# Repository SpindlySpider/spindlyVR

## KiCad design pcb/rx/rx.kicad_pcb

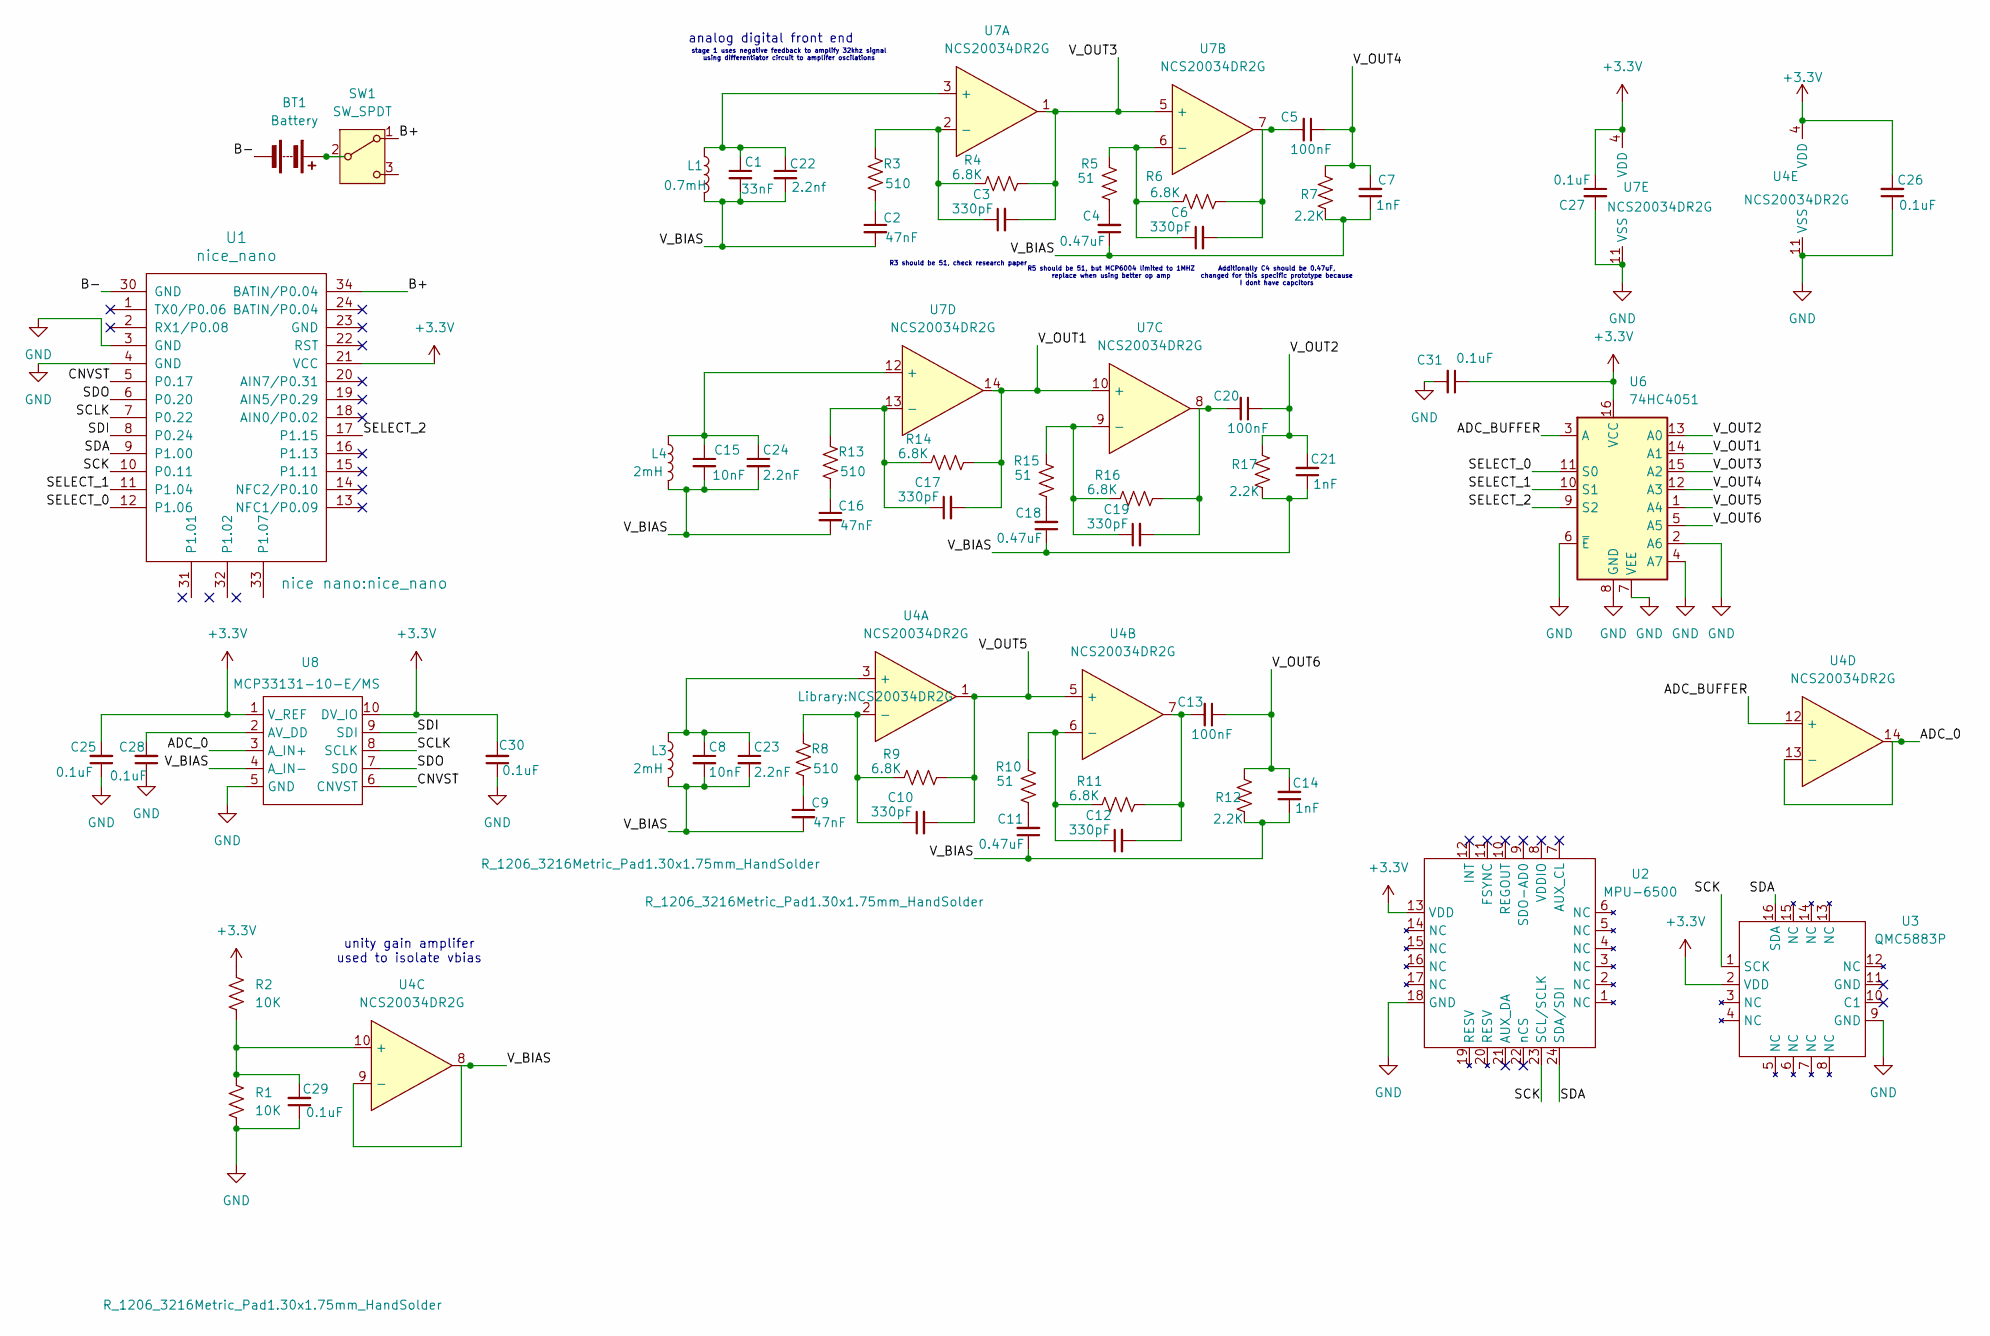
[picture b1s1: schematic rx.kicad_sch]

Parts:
BT1: Battery; JST_PH_B2B-PH-K_1x02_P2.00mm_Vertical
C1: 33nF; C_1206_3216Metric_Pad1.33x1.80mm_HandSolder
C2, C9, C16: 47nF; C_1206_3216Metric_Pad1.33x1.80mm_HandSolder
C3, C6, C10, C12, C17, C19: 330pF; C_1206_3216Metric_Pad1.33x1.80mm_HandSolder
C4, C11, C18: 0.47uF; C_1206_3216Metric_Pad1.33x1.80mm_HandSolder
C5, C13, C20: 100nF; C_1206_3216Metric_Pad1.33x1.80mm_HandSolder
C7, C14, C21: 1nF; C_1206_3216Metric_Pad1.33x1.80mm_HandSolder
C8, C15: 10nF; C_1206_3216Metric_Pad1.33x1.80mm_HandSolder
C22: 2.2nf; C_1206_3216Metric_Pad1.33x1.80mm_HandSolder
C23, C24: 2.2nF; C_1206_3216Metric_Pad1.33x1.80mm_HandSolder
C25, C26, C27, C28, C29, C30, C31: 0.1uF; C_1206_3216Metric_Pad1.33x1.80mm_HandSolder
L1: 0.7mH; R_1206_3216Metric_Pad1.30x1.75mm_HandSolder
L3, L4: 2mH; R_1206_3216Metric_Pad1.30x1.75mm_HandSolder
R1, R2: 10K; R_1206_3216Metric_Pad1.30x1.75mm_HandSolder
R3, R8, R13: 510; R_1206_3216Metric_Pad1.30x1.75mm_HandSolder
R4, R6, R9, R11, R14, R16: 6.8K; R_1206_3216Metric_Pad1.30x1.75mm_HandSolder
R5, R10, R15: 51; R_1206_3216Metric_Pad1.30x1.75mm_HandSolder
R7, R12, R17: 2.2K; R_1206_3216Metric_Pad1.30x1.75mm_HandSolder
SW1: SW_SPDT; EG1218
U1: nice_nano
U2: MPU-6500
U3: QMC5883P
U4, U7: NCS20034DR2G
U6: 74HC4051; 74HC4051-chip
U8: MCP33131-10-E/MS; MCP33131

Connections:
+3.3V: C25.2, C26.2, C27.1, C30.2, C31.1, R2.1, U1.21 (VCC), U2.13 (VDD), U3.2 (VDD), U4.4 (VDD), U6.16 (VCC), U7.4 (VDD), U8.1 (V_REF), U8.10 (DV_IO)
/ADC_0: U4.13 (-), U4.14, U8.3 (A_IN+)
/ADC_BUFFER: U4.12 (+), U6.3 (A)
/B+: SW1.1 (A), U1.34 (BATIN/P0.04)
/B-: BT1.2 (-), U1.30 (GND)
/CNVST: U1.5 (P0.17), U8.6 (CNVST)
/SCK: U1.10 (P0.11), U2.23 (SCL/SCLK), U3.1 (SCK)
/SCLK: U1.7 (P0.22), U8.8 (SCLK)
/SDA: U1.9 (P1.00), U2.24 (SDA/SDI), U3.16 (SDA)
/SDI: U1.8 (P0.24), U8.9 (SDI)
/SDO: U1.6 (P0.20), U8.7 (SDO)
/SELECT_0: U1.12 (P1.06), U6.11 (S0)
/SELECT_1: U1.11 (P1.04), U6.10 (S1)
/SELECT_2: U1.17 (P1.15), U6.9 (S2)
/V_BIAS: C1.2, C2.2, C4.1, C7.1, C8.2, C9.2, C11.1, C14.1, C15.2, C16.2, C18.1, C21.1, C22.2, C23.2, C24.2, L1.2, L3.2, L4.2, R7.2, R12.2, R17.2, U4.8, U4.9 (-), U8.4 (A_IN-)
/V_OUT1: C17.2, R14.1, U6.14 (A1), U7.10 (+), U7.14
/V_OUT2: C20.1, C21.2, R17.1, U6.13 (A0)
/V_OUT3: C3.2, R4.1, U6.15 (A2), U7.1, U7.5 (+)
/V_OUT4: C5.1, C7.2, R7.1, U6.12 (A3)
/V_OUT5: C10.2, R9.1, U4.1, U4.5 (+), U6.1 (A4)
/V_OUT6: C13.1, C14.2, R12.1, U6.5 (A5)
GND: C25.1, C26.1, C27.2, C28.1, C29.1, C30.1, C31.2, R1.2, U1.3 (GND), U1.4 (GND), U2.18 (GND), U3.9 (GND), U4.11 (VSS), U6.2 (A6), U6.4 (A7), U6.6 (~E), U6.7 (VEE), U6.8 (GND), U7.11 (VSS), U8.5 (GND)
unnamed: BT1.1 (+), SW1.2 (B)
unnamed: C2.1, R3.2
unnamed: C4.2, R5.2
unnamed: C5.2, C6.2, R6.1, U7.7
unnamed: C9.1, R8.2
unnamed: C11.2, R10.2
unnamed: C12.2, C13.2, R11.1, U4.7
unnamed: C16.1, R13.2
unnamed: C18.2, R15.2
unnamed: C19.2, C20.2, R16.1, U7.8
unnamed: C8.1, C23.1, L3.1, U4.3 (+)
unnamed: C10.1, R8.1, R9.2, U4.2 (-)
unnamed: C12.1, R10.1, R11.2, U4.6 (-)
unnamed: C29.2, R1.1, R2.2, U4.10 (+)
unnamed: C1.1, C22.1, L1.1, U7.3 (+)
unnamed: C3.1, R3.1, R4.2, U7.2 (-)
unnamed: C6.1, R5.1, R6.2, U7.6 (-)
unnamed: C19.1, R15.1, R16.2, U7.9 (-)
unnamed: C15.1, C24.1, L4.1, U7.12 (+)
unnamed: C17.1, R13.1, R14.2, U7.13 (-)
unnamed: C28.2, U8.2 (AV_DD)

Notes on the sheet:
unity gain amplifer used to isolate vbias
R5 should be 51, but MCP6004 limited to 1MHZ replace when using better op amp
analog digital front end
stage 1 uses negative feedback to amplify 32khz signal using differentiator circuit to amplifer oscilations
Additionally C4 should be 0.47uF, changed for this specific prototype because I dont have capcitors
R3 should be 51, check research paper

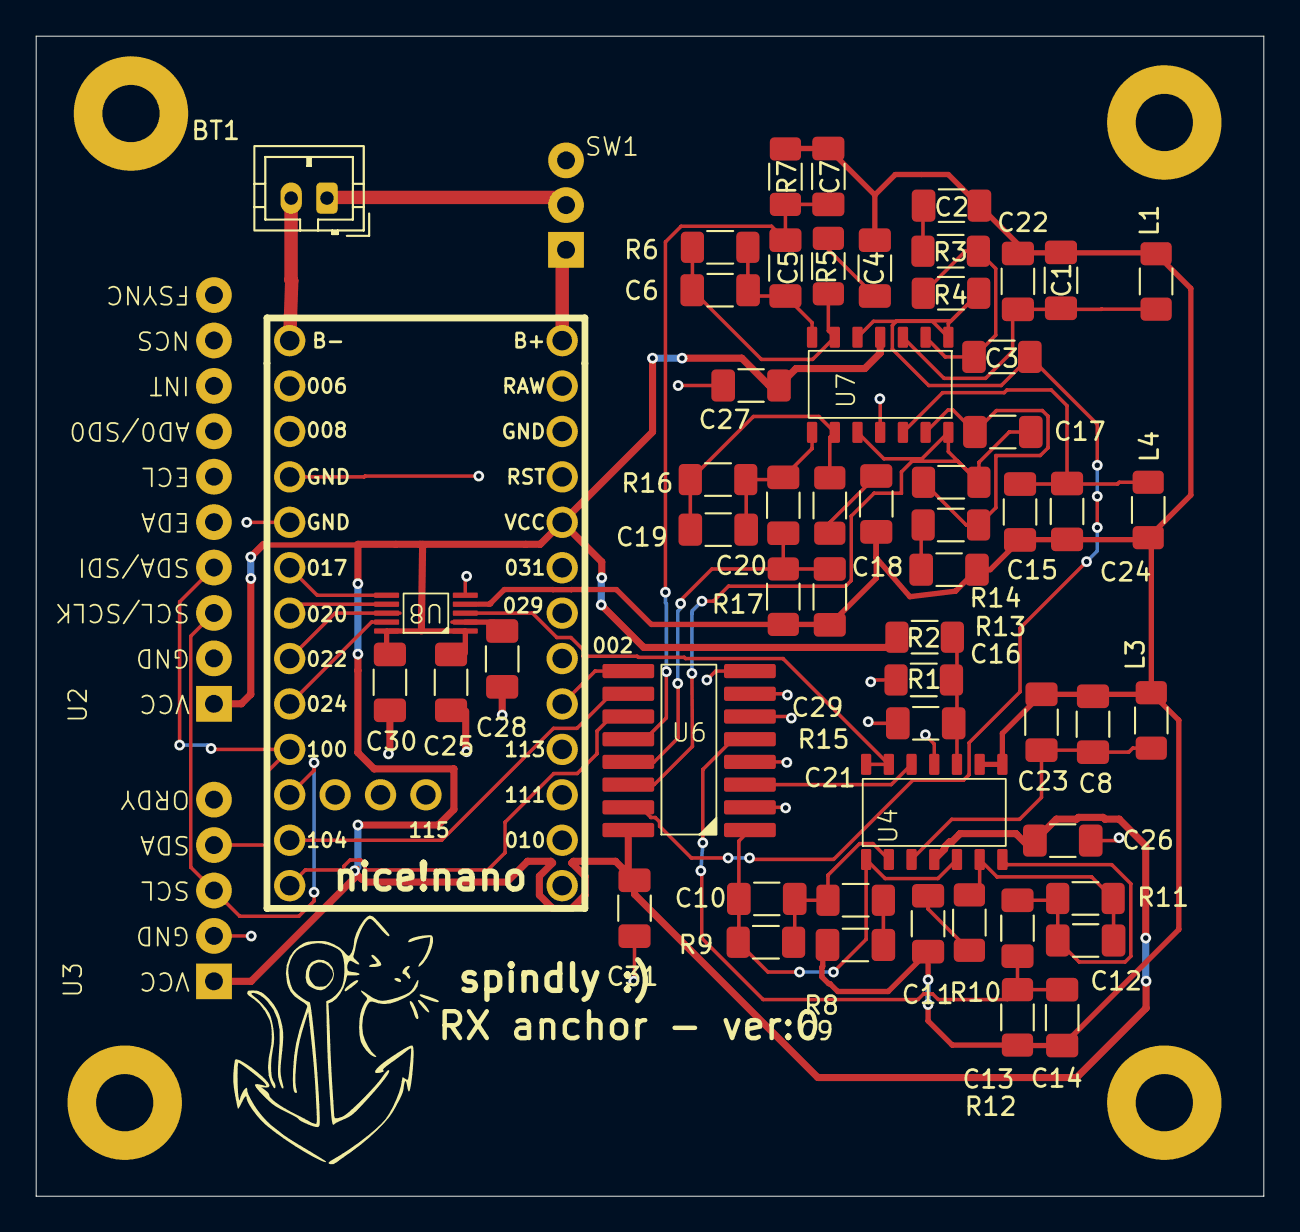
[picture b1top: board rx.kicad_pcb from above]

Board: 2 copper layers, 68.7 x 64.9 mm, 60 parts (0 on the bottom side), 43 nets.

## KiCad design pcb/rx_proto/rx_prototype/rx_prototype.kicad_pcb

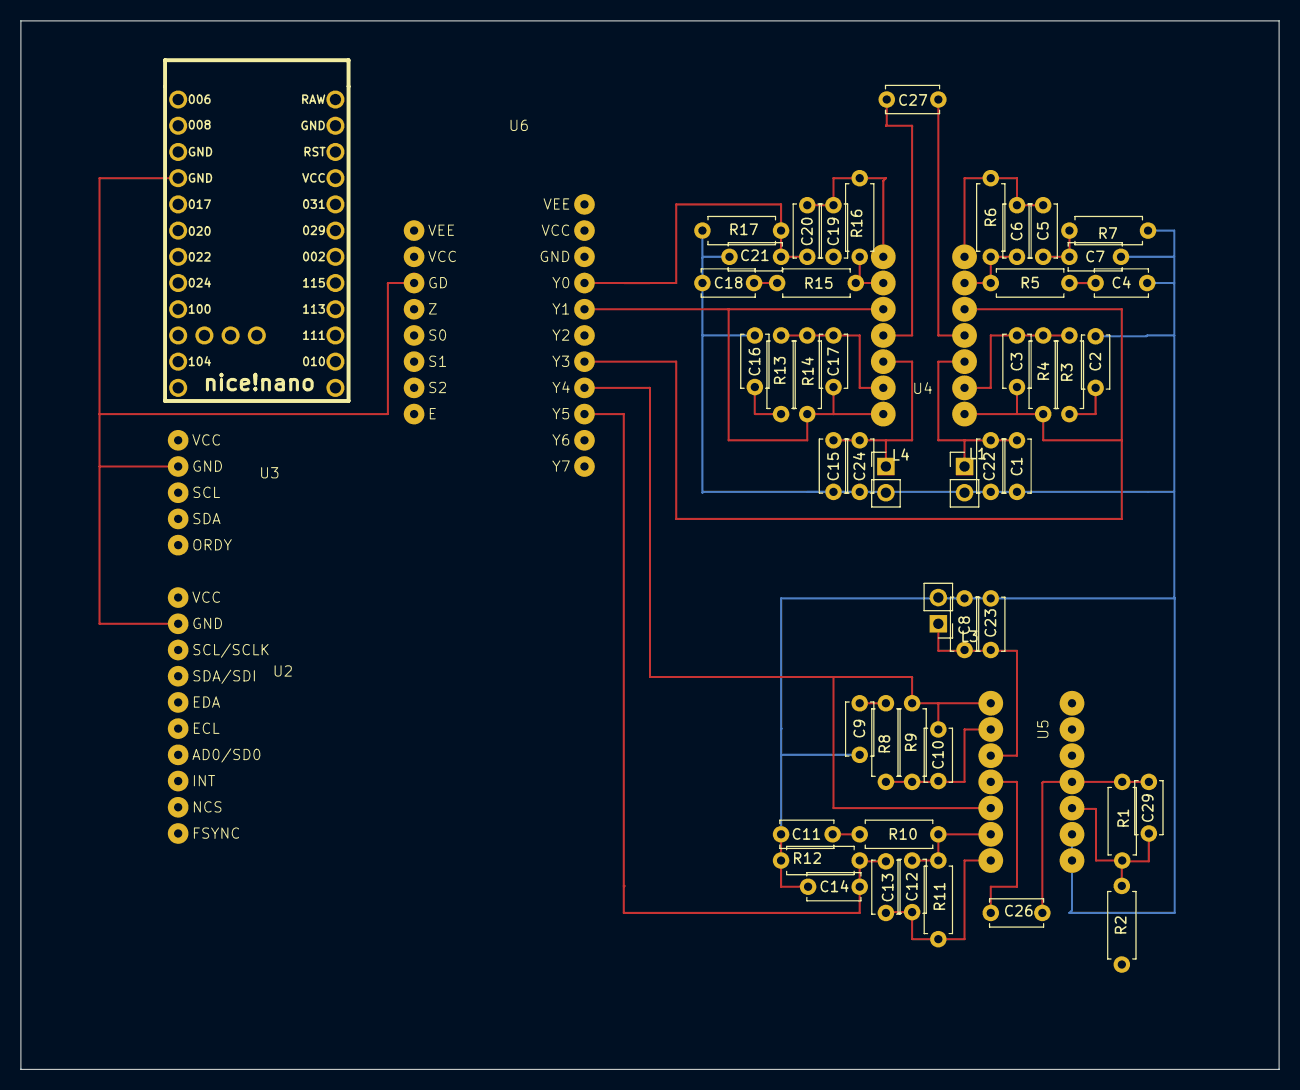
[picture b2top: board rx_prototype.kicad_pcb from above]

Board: 10 copper layers, 121.9 x 101.6 mm, 53 parts (0 on the bottom side), 35 nets.

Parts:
C1: 33nF; C_Disc_D5.0mm_W2.5mm_P5.00mm
C2, C9, C16: 47nF; C_Disc_D5.0mm_W2.5mm_P5.00mm
C3, C6, C10, C12, C17, C19: 330pF; C_Disc_D5.0mm_W2.5mm_P5.00mm
C4, C11, C18, C26, C27, C29: 0.1uF; C_Disc_D5.0mm_W2.5mm_P5.00mm
C5, C13, C20: 100nF; C_Disc_D5.0mm_W2.5mm_P5.00mm
C7, C14, C21: 1nF; C_Disc_D5.0mm_W2.5mm_P5.00mm
C8, C15: 10nF; C_Disc_D5.0mm_W2.5mm_P5.00mm
C22: 2.2nf; C_Disc_D5.0mm_W2.5mm_P5.00mm
C23, C24: 2.2nF; C_Disc_D5.0mm_W2.5mm_P5.00mm
L1: 0.7mH; PinHeader_1x02_P2.54mm_Vertical
L3, L4: 2mH; PinHeader_1x02_P2.54mm_Vertical
R1, R2: 10K; R_Axial_DIN0207_L6.3mm_D2.5mm_P7.62mm_Horizontal
R3, R5, R8, R10, R13, R15: 750; R_Axial_DIN0207_L6.3mm_D2.5mm_P7.62mm_Horizontal
R4, R6, R9, R11, R14, R16: 6.8K; R_Axial_DIN0207_L6.3mm_D2.5mm_P7.62mm_Horizontal
R7, R12, R17: 2.2K; R_Axial_DIN0207_L6.3mm_D2.5mm_P7.62mm_Horizontal
U1: nice_nano
U2: MPU-6500
U3: QMC5883P
U4, U5: MCP6004
U6: 74HC4051

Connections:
+3.3V: C26.2, C27.1, R2.1, U1.21 (VCC), U2.13 (VDD), U3.2 (VDD), U4.4 (V+), U5.4 (V+), U6.16 (VCC)
/ADC_0: U1.18 (AIN0/P0.02), U5.13 (-), U5.14
/ADC_BUFFER: U5.12 (+), U6.3 (A)
/SCK: U1.6 (P0.20), U2.23 (SCL/SCLK), U3.1 (SCK)
/SDA: U1.5 (P0.17), U2.24 (SDA/SDI), U3.16 (SDA)
/SELECT_0: U1.15 (P1.11), U6.11 (S0)
/SELECT_1: U1.14 (NFC2/P0.10), U6.10 (S1)
/SELECT_2: U1.13 (NFC1/P0.09), U6.9 (S2)
/V_BIAS: C1.2, C2.2, C4.1, C7.1, C8.2, C9.2, C11.1, C14.1, C15.2, C16.2, C18.1, C21.1, C22.2, C23.2, C24.2, L1.2, L3.2, L4.2, R7.2, R12.2, R17.2, U5.8, U5.9 (-)
/V_OUT1: C17.2, R14.1, U4.10 (+), U4.14, U6.14 (A1)
/V_OUT2: C20.1, C21.2, R17.1, U6.13 (A0)
/V_OUT3: C3.2, R4.1, U4.1, U4.5 (+), U6.12 (A3)
/V_OUT4: C5.1, C7.2, R7.1, U6.15 (A2)
/V_OUT5: C10.2, R9.1, U5.1, U5.5 (+), U6.1 (A4)
/V_OUT6: C13.1, C14.2, R12.1, U6.5 (A5)
GND: C26.1, C27.2, C29.1, R1.2, U1.3 (GND), U1.4 (GND), U2.18 (GND), U3.9 (GND), U4.11 (V-), U5.11 (V-), U6.2 (A6), U6.4 (A7), U6.6 (~E), U6.7 (VEE), U6.8 (GND)
unnamed: C2.1, R3.2
unnamed: C4.2, R5.2
unnamed: C5.2, C6.2, R6.1, U4.7
unnamed: C9.1, R8.2
unnamed: C11.2, R10.2
unnamed: C12.2, C13.2, R11.1, U5.7
unnamed: C16.1, R13.2
unnamed: C18.2, R15.2
unnamed: C19.2, C20.2, R16.1, U4.8
unnamed: C1.1, C22.1, L1.1, U4.3 (+)
unnamed: C3.1, R3.1, R4.2, U4.2 (-)
unnamed: C6.1, R5.1, R6.2, U4.6 (-)
unnamed: C19.1, R15.1, R16.2, U4.9 (-)
unnamed: C15.1, C24.1, L4.1, U4.12 (+)
unnamed: C17.1, R13.1, R14.2, U4.13 (-)
unnamed: C8.1, C23.1, L3.1, U5.3 (+)
unnamed: C10.1, R8.1, R9.2, U5.2 (-)
unnamed: C12.1, R10.1, R11.2, U5.6 (-)
unnamed: C29.2, R1.1, R2.2, U5.10 (+)

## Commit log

2025-11-26 Start zephyr
2025-11-26 Updated ignore to ignore zephyr files
2025-11-27 Moved stepper motor code
2025-11-27 Update ignore
2025-11-27 Moved code up
2025-11-27 Update main code
2025-11-27 Updated code to drive stepper
2025-11-28 Added spool 3d models
2025-11-29 Update design of triaxis magnet
    Updated design adding:
    - mounting holes
    - curve for easier routing of wire
2025-11-30 Updated to make parametric work
2025-11-30 Updated spool models
2025-11-30 Updated Code for stepper motor driving
2025-11-30 Update code
2025-11-30 Updated code to allow for speed up and speed down of stepper motor
    this prevents jittering issue
2025-11-30 Enabled GPIO 0
2025-12-03 Moved tri-axis magnet
2025-12-04 Add new version tri-axis reciver
2025-12-04 Increase ramp up time
2025-12-07 Added version 4 parts
2025-12-07 Updated ignore to include 3d files
2025-12-09 Backup for transmittor code
2025-12-09 Added small driver for qmc5883p
2025-12-10 Added new offsets
2025-12-10 Moved files in to seperate sources
2025-12-10 Working with filter
2025-12-11 Update to fix madgwick filter
2026-03-05 Backup
2026-03-05 Initial bluetooth work
2026-03-06 Transmit data working
2026-03-06 Receiver complete
2026-03-07 Started work on ADC for phase and amp
2026-03-07 Multi threading woking
2026-03-08 Moved common files to common dir
2026-03-11 working ADC
2026-03-11 Remove receive data
2026-03-11 Clean up ADC code
2026-03-11 Update ADC to use NRFX timer properly
2026-03-12 Update to use ESB protocol instead of BLE
2026-03-12 Fixed ADC & ESB
    issue:
    - timer 2 was being used by ESB causing ADC to not work so switched to
    timer 3
    - Added .clangd for lsp
    - Tx was not working because of `selective_auto_ack` not being enabled
2026-03-12 Update common for Rx & TX
2026-03-12 Init work on reciever
2026-03-12 Update Rx data manipulation
2026-03-12 ADC switching
    Added ADC switching to read from 3 different ADC sources
2026-03-15 Update spool size Tx was too weak
    - this is slightly bigger Tx to increase area, it may need to be
    increased further in the future
2026-03-15 Removed PWM from receiver board
2026-03-15 Update reciever to include differntal mode and debug
2026-03-15 Fixed transmitter
    - PWM coil 2 was set to invert to maximuse H bridge useage
2026-03-27 Added symbols for op amp and adc
2026-03-29 Fixed Tx phase and amp calc
2026-03-29 Added new symbols
2026-03-29 Save progress of prototype board
2026-03-29 Back up prototype
2026-03-29 Another prototype backup
2026-03-30 Update wiring
    capcitors were in parallel would cause DC blocking
2026-03-30 Update prototype to include footprints for perfboard layout
2026-03-31 Update perfboard layout
2026-03-31 Update perf layout
2026-03-31 Update perf
2026-03-31 Completed perboard prototype
2026-03-31 Compacted Perfboard
2026-03-31 Backup Prototype
2026-04-02 Update perfboard prototype front end
2026-04-03 Created rx board for order
2026-04-03 Finished Rx
2026-04-04 Backup from work
2026-04-05 Update Rx board to include anchor
2026-04-20 Update to include phase sync
    lots of work went into this one,
    new syncing over ESB, (could be done over bluetooth)
    not relying on CPU to wake up instead update last messages phase
2026-04-21 Update to include positoning data
    currently not fully functional, the phase drift issue still occurs need
    to fix this, but it is progress
2026-04-22 Update to use correct orientation
2026-04-24 Update broken transmitter
2026-05-04 Update visaliser to use vispy
2026-05-05 Update the receiver and visualiser, such that phase sync can be monitored and orientation can be checked
2026-05-10 File cleanup
2026-05-10 Reduce duty cycle for compliance
    driving at 3.3V and 0.5 duty cycle was above 150mA RMS
    Update to include pin sleep
2026-05-10 Update ADC to clean up code and improve functionality
    implemeted dynamic coil selection, sign extraction is much more stable
2026-05-10 Added calibration script
    Update formatting
2026-05-10 Updated positioning code
2026-05-10 Update coil calibration script & coil gain
2026-05-10 Implemented pos
2026-05-10 Fixed positioning 0 issue
    now need to fix the jitter mess
2026-05-11 Update helper scripts
2026-05-11 Include quaternions & update postion algo for 4 octant
2026-05-12 Add kalman noise finder
2026-05-12 Removed dynamic coil switching
    issues where the sign was not anchored
2026-05-13 Added gyro bias calibration at startup
2026-05-13 Add calibration button
2026-05-14 Added grid calibration helper
2026-05-14 Added helper scripts for grid calibration
2026-05-15 Create LICENSE
2026-05-19 Removed text file
